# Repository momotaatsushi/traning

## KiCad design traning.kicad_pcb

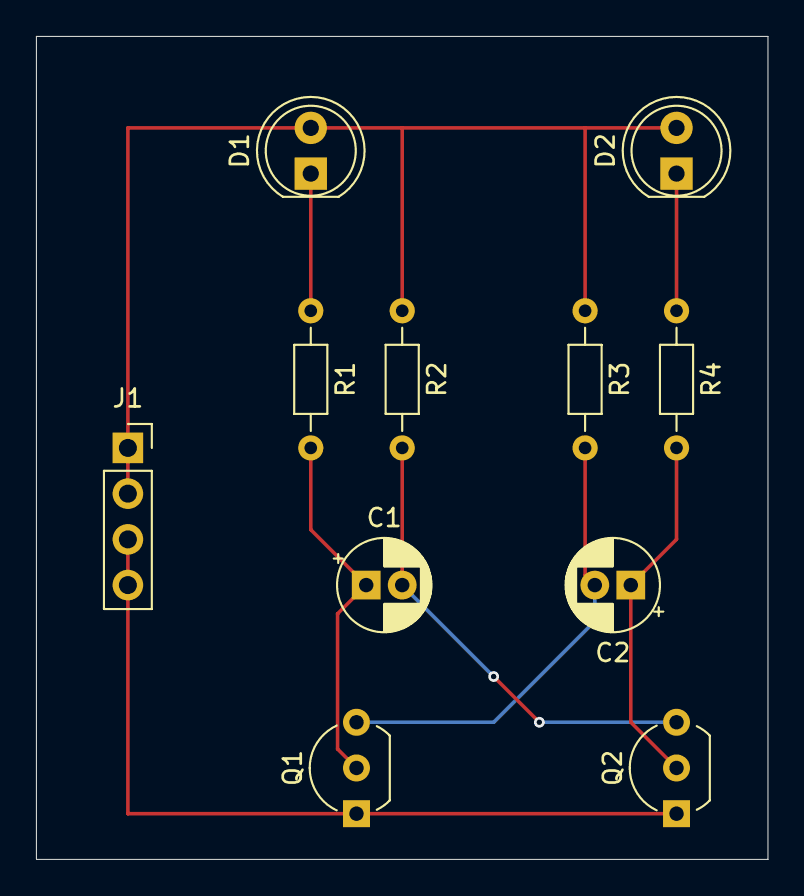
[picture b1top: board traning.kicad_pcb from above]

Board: 2 copper layers, 40.6 x 45.7 mm, 11 parts (0 on the bottom side), 8 nets.

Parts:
C1, C2: C; CP_Radial_D5.0mm_P2.00mm
D1, D2: LED; LED_D5.0mm
J1: Conn_01x04_Socket; PinSocket_1x04_P2.54mm_Vertical
Q1, Q2: 2SC1815; TO-92_Inline_Wide
R1, R2, R3, R4: R; R_Axial_DIN0204_L3.6mm_D1.6mm_P7.62mm_Horizontal

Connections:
+5V: D1.2 (A), D2.2 (A), J1.1, J1.2, R2.1, R3.1
GND: J1.3, J1.4, Q1.1 (E), Q2.1 (E)
unnamed: D1.1 (K), R1.1
unnamed: D2.1 (K), R4.1
unnamed: C2.2, Q1.3 (B), R3.2
unnamed: C1.1, Q1.2 (C), R1.2
unnamed: C1.2, Q2.3 (B), R2.2
unnamed: C2.1, Q2.2 (C), R4.2

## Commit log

2024-11-22 プロジェクト作成
2024-11-22 回路図作成
2024-11-22 部品割り当て
2024-11-22 基板設計
2024-11-28 未配線箇所を配線
2024-11-28 配線を修正
